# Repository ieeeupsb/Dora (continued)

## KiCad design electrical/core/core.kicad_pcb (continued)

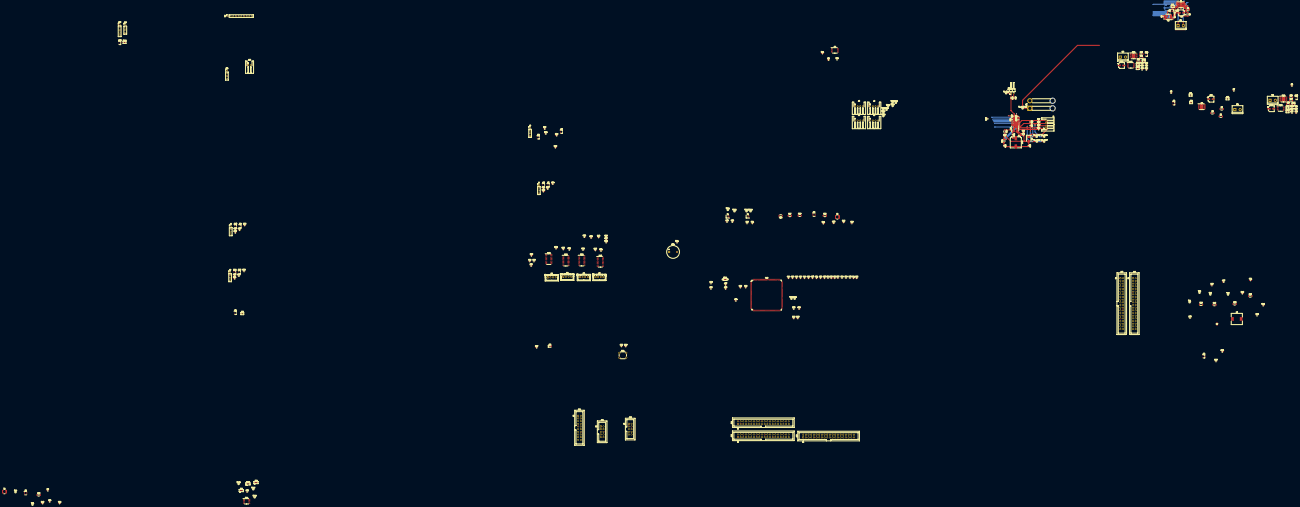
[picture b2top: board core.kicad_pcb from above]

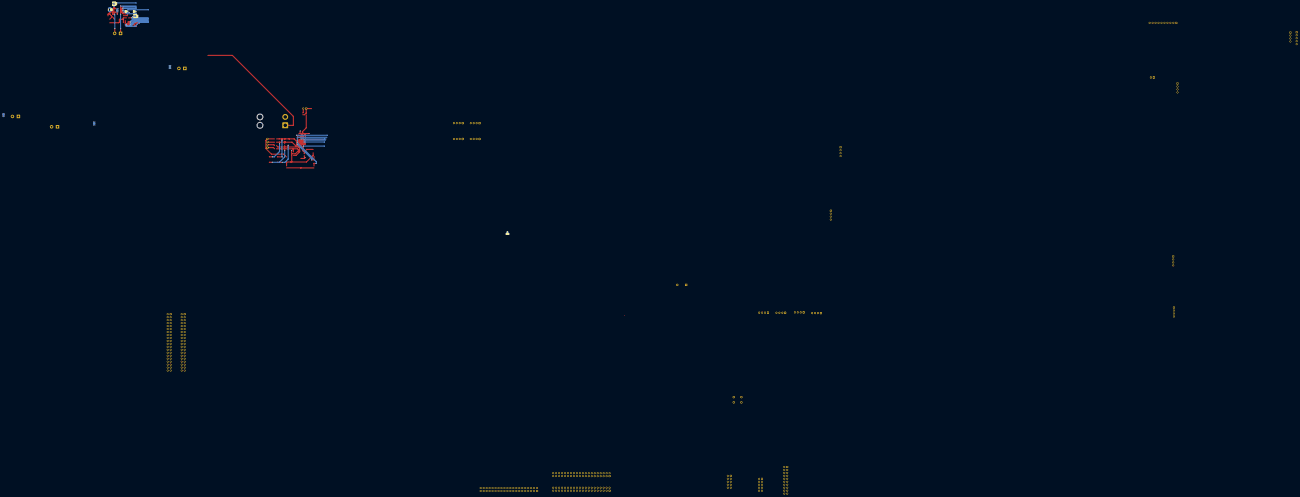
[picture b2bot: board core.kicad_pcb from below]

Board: 4 copper layers, 281 parts (6 on the bottom side), 318 nets.

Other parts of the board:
TP_BATT+1: TestPoint; TestPoint_Pad_D1.0mm

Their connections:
+BATT: TP_BATT+1.1; also elsewhere on the board

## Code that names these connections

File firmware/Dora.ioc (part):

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Mcu.Name=STM32F469IITx
Mcu.Package=LQFP176
Mcu.UserName=STM32F469IITx
PA0/WKUP.Signal=ADCx_IN0
PA1.Signal=S_TIM2_CH2
PA10.Mode=Asynchronous
PA10.Signal=USART1_RX
PA13.Mode=JTAG_5_pins
PA13.Signal=SYS_JTMS-SWDIO
PA14.Mode=JTAG_5_pins
PA14.Signal=SYS_JTCK-SWCLK
PA15.Mode=JTAG_5_pins
PA15.Signal=SYS_JTDI
PA2.Signal=ADCx_IN2
PA3.Signal=ADCx_IN3
PA4.Mode=Slave_8_bits_External_Synchro
PA4.Signal=DCMI_HSYNC
PA5.Signal=S_TIM2_CH1_ETR
PA6.Mode=Slave_8_bits_External_Synchro
PA6.Signal=DCMI_PIXCLK
PA7.Signal=ADCx_IN7
PA9.Mode=Asynchronous
PA9.Signal=USART1_TX
PB0.Signal=ADCx_IN8
PB1.Signal=ADCx_IN9
PB10.Signal=S_TIM2_CH3
PB11.Signal=S_TIM2_CH4
PB13.Mode=Full_Duplex_Master
PB13.Signal=SPI2_SCK
PB14.Mode=Full_Duplex_Master
PB14.Signal=SPI2_MISO
PB15.Mode=Full_Duplex_Master
PB15.Signal=SPI2_MOSI
PB2/BOOT1.GPIOParameters=GPIO_Label
PB2/BOOT1.GPIO_Label=Motor2_IMODE
PB2/BOOT1.Signal=GPIO_Output
PB3.Mode=JTAG_5_pins
PB3.Signal=SYS_JTDO-SWO
PB4.Mode=JTAG_5_pins
PB4.Signal=SYS_JTRST
PB6.Mode=I2C
PB6.Signal=I2C1_SCL
PB7.Mode=I2C
PB7.Signal=I2C1_SDA
PB8.Mode=Slave_8_bits_External_Synchro
PB8.Signal=DCMI_D6
PB9.Mode=Slave_8_bits_External_Synchro
PB9.Signal=DCMI_D7
PC0.Signal=ADCx_IN10
PC1.Signal=ADCx_IN11
PC14/OSC32_IN.Mode=LSE-External-Oscillator
PC14/OSC32_IN.Signal=RCC_OSC32_IN
PC15/OSC32_OUT.Mode=LSE-External-Oscillator
PC15/OSC32_OUT.Signal=RCC_OSC32_OUT
PC2.Signal=ADCx_IN12
PC3.Signal=ADCx_IN13
PC4.Signal=ADCx_IN14
PC5.Signal=ADCx_IN15
PC6.Mode=Slave_8_bits_External_Synchro
PC6.Signal=DCMI_D0
PC7.Mode=Slave_8_bits_External_Synchro
PC7.Signal=DCMI_D1
PC8.Mode=Slave_8_bits_External_Synchro
PC8.Signal=DCMI_D2
PC9.Mode=Slave_8_bits_External_Synchro
PC9.Signal=DCMI_D3
PD10.GPIOParameters=GPIO_Label
PD10.GPIO_Label=D2_DigiPot_WLAT
PD10.Signal=GPIO_Output
PD11.GPIOParameters=GPIO_Label
PD11.GPIO_Label=D2_DigiPot_SHDN
PD11.Signal=GPIO_Output
PD3.Mode=Slave_8_bits_External_Synchro
PD3.Signal=DCMI_D5
PD8.GPIOParameters=GPIO_Label
PD8.GPIO_Label=D1_DigiPot_WLAT
PD8.Signal=GPIO_Output
PD9.GPIOParameters=GPIO_Label
PD9.GPIO_Label=D1_DigiPot_SHDN
PD9.Signal=GPIO_Output
PE11.Signal=S_TIM1_CH2
PE13.Signal=S_TIM1_CH3
PE14.Signal=S_TIM1_CH4
PE4.Mode=Slave_8_bits_External_Synchro
PE4.Signal=DCMI_D4
PE5.Signal=S_TIM9_CH1
PE6.Signal=S_TIM9_CH2
PE7.GPIOParameters=GPIO_Label
PE7.GPIO_Label=Motor1_nFAULT
PE7.Signal=GPIO_Input
PE8.GPIOParameters=GPIO_Label
PE8.GPIO_Label=Motor1_IMODE
PE8.Signal=GPIO_Output
PE9.Signal=S_TIM1_CH1
PF0.Mode=I2C
PF0.Signal=I2C2_SDA
PF1.Mode=I2C
PF1.Signal=I2C2_SCL
PF10.GPIOParameters=GPIO_Label
PF10.GPIO_Label=Driver_Current_Limit_CS2
PF10.Signal=GPIO_Output
PF11.GPIOParameters=GPIO_Label
PF11.GPIO_Label=Motor2_nSLEEP
PF11.Signal=GPIO_Output
PF12.GPIOParameters=GPIO_Label
PF12.GPIO_Label=Motor2_PMODE
PF12.Signal=GPIO_Output
PF13.GPIOParameters=GPIO_Label
PF13.GPIO_Label=Motor2_nFAULT
PF13.Signal=GPIO_Input
PF14.GPIOParameters=GPIO_Label
PF14.GPIO_Label=Motor1_nSLEEP
PF14.Signal=GPIO_Output
PF15.GPIOParameters=GPIO_Label
PF15.GPIO_Label=Motor1_PMODE
PF15.Signal=GPIO_Output
PF2.Signal=GPIO_Input
PF3.Signal=GPIO_Input
PF4.Signal=GPIO_Input
PF5.Signal=GPIO_Input
PF6.Signal=S_TIM10_CH1
PF7.Signal=GPIO_Input
PF8.Signal=GPIO_Input
PF9.GPIOParameters=GPIO_Label
PF9.GPIO_Label=Driver_Current_Limit_CS1
PF9.Signal=GPIO_Output
PG0.GPIOParameters=GPIO_Label
PG0.GPIO_Label=Rotary_SW
PG0.Signal=GPIO_Input
PG1.GPIOParameters=GPIO_Label
PG1.GPIO_Label=Rotary_CLK
PG1.Signal=GPIO_Input
PG10.GPIOParameters=GPIO_Label
PG10.GPIO_Label=IR_SEL0
PG10.Signal=GPIO_Output
PG11.GPIOParameters=GPIO_Label
PG11.GPIO_Label=IR_SEL1
PG11.Signal=GPIO_Output
PG12.GPIOParameters=GPIO_Label
PG12.GPIO_Label=IR_SEL2
PG12.Signal=GPIO_Output
PG13.GPIOParameters=GPIO_Label
PG13.GPIO_Label=WP
PG13.Signal=GPIO_Output
PG14.GPIOParameters=GPIO_Label
PG14.GPIO_Label=Battery_Overcurrent
PG14.Signal=GPIO_Input
PG2.GPIOParameters=GPIO_Label
PG2.GPIO_Label=Rotary_DT
PG2.Signal=GPIO_Input
PG3.GPIOParameters=GPIO_Label
PG3.GPIO_Label=LEFT_ENC1
PG3.Signal=GPIO_Input
PG4.GPIOParameters=GPIO_Label
PG4.GPIO_Label=LEFT_ENC2
PG4.Signal=GPIO_Input
PG5.GPIOParameters=GPIO_Label
PG5.GPIO_Label=RIGHT_ENC1
PG5.Signal=GPIO_Input
PG6.GPIOParameters=GPIO_Label
PG6.GPIO_Label=RIGHT_ENC2
PG6.Signal=GPIO_Input
PG9.Mode=Slave_8_bits_External_Synchro
PG9.Signal=DCMI_VSYNC
PH0/OSC_IN.Mode=HSE-External-Oscillator
PH0/OSC_IN.Signal=RCC_OSC_IN
PH1/OSC_OUT.Mode=HSE-External-Oscillator
PH1/OSC_OUT.Signal=RCC_OSC_OUT
PH2.GPIOParameters=GPIO_Label
PH2.GPIO_Label=OLED_EN
PH2.Signal=GPIO_Output
PH3.GPIOParameters=GPIO_Label
PH3.GPIO_Label=Ultra_EN
PH3.Signal=GPIO_Output
PH4.GPIOParameters=GPIO_Label
PH4.GPIO_Label=IR_EN
PH4.Signal=GPIO_Output
PH5.GPIOParameters=GPIO_Label
PH5.GPIO_Label=RPi_EN
PH5.Signal=GPIO_Output
PH6.GPIOParameters=GPIO_Label
PH6.GPIO_Label=Camera_EN
PH6.Signal=GPIO_Output
PH7.GPIOParameters=GPIO_Label
PH7.GPIO_Label=LoRa_EN
PH7.Signal=GPIO_Output
PI0.GPIOParameters=GPIO_Label
PI0.GPIO_Label=Ultra1_TRIG
PI0.Signal=GPIO_Output
PI1.GPIOParameters=GPIO_Label
PI1.GPIO_Label=Ultra1_ECHO
PI1.Signal=GPIO_Input
PI3.GPIOParameters=GPIO_Label
PI3.GPIO_Label=Ultra2_TRIG
PI3.Signal=GPIO_Output
PI4.GPIOParameters=GPIO_Label
PI4.GPIO_Label=Ultra2_ECHO
PI4.Signal=GPIO_Input
PI5.GPIOParameters=GPIO_Label
PI5.GPIO_Label=Ultra3_TRIG
PI5.Signal=GPIO_Output
PI6.GPIOParameters=GPIO_Label
PI6.GPIO_Label=Ultra3_ECHO
PI6.Signal=GPIO_Input
PI7.GPIOParameters=GPIO_Label
PI7.GPIO_Label=Ultra4_TRIG
PI7.Signal=GPIO_Output
PI8.GPIOParameters=GPIO_Label
PI8.GPIO_Label=Ultra4_ECHO
PI8.Signal=GPIO_Input
RCC.SYSCLKFreq_VALUE=180000000
RCC.SYSCLKSource=RCC_SYSCLKSOURCE_PLLCLK
board=custom

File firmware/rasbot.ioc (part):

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Mcu.Name=STM32F103C(8-B)Tx
Mcu.Package=LQFP48
Mcu.UserName=STM32F103C8Tx
PA13.Mode=Serial_Wire
PA13.Signal=SYS_JTMS-SWDIO
PA14.Mode=Serial_Wire
PA14.Signal=SYS_JTCK-SWCLK
PC14-OSC32_IN.Mode=LSE-External-Oscillator
PC14-OSC32_IN.Signal=RCC_OSC32_IN
PC15-OSC32_OUT.Mode=LSE-External-Oscillator
PC15-OSC32_OUT.Signal=RCC_OSC32_OUT
PD0-OSC_IN.Mode=HSE-External-Oscillator
PD0-OSC_IN.Signal=RCC_OSC_IN
PD1-OSC_OUT.Mode=HSE-External-Oscillator
PD1-OSC_OUT.Signal=RCC_OSC_OUT
RCC.SYSCLKFreq_VALUE=72000000
RCC.SYSCLKSource=RCC_SYSCLKSOURCE_PLLCLK
board=custom

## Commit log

2019-06-19 Backlink to CADLAB.io has been added.
2019-06-19 [PCB] Project Initialization
2019-06-20 [Firmware] Skeleton Code
2019-06-20 [PCB] MCU Decoupling Capacitors
2019-06-20 [PCB] MCU Crystal
2019-06-20 [Firmware] Ignore Eclipse Files
2019-06-20 [PCB] Assign Footprints
2019-06-20 [PCB & Firmware] SWD Interface
2019-06-20 [PCB] Reset Button, Power LED, BOOT pins and LSE Crystal
2019-06-20 [PCB] Crystal Capacitor Sizing
2019-06-20 [PCB & Firmware] SWD Connector and Reset Button Footprint and Firmware LSE Enable
2019-06-20 [PCB] Connect LSE to MCU
2019-06-20 [PCB & Firmware] Motors PWM Signal MCU Pins
2019-06-20 [PCB & Firmware] Line Sensors MCU Pins
2019-06-20 [PCB & Firmware] I2C for LCD SSD1306 MCU Pins
2019-06-20 [PCB & Firmware] Light Sensor MCU Pin
2019-06-26 IR matrix
2019-07-07 Infrared index starts at 0
2019-07-09 Use Buses for IR sensors
2019-07-22 IR matrix complete minus control transistor
2019-07-22 AO3400 Symbol added to library
2019-07-22 MOSFET model added
2019-07-22 IR Matrix - Missing Supply Connection
2019-07-22 Initial Symbol for DRV8873S
2019-07-24 Resistor value corrected
2019-07-25 Added 0 ohm resistor to power switch
2019-07-25 Fixed AO3400 symbol
2019-07-25 Fixed DRV8873 symbol
2019-07-25 Buzzer and RGB LED interfaces
2019-07-25 Increased Resistance
2019-07-26 Description of the project
2019-07-26 Notes about branch protections
2019-07-27 STM32F407 and JLink
2019-07-28 Connect IR Matrix to MCU
2019-07-28 Optimized IR MCU pins
2019-07-28 Size Crystals
2019-07-28 Fix IR Sensors
2019-07-28 Grammar revision
2019-07-28 Fix resistor IR Matrix
2019-07-28 Added BQ76925 KiCAD symbol
2019-07-28 Fix Merges
2019-07-28 Clean Project
2019-07-28 Fix and Anotate design
2019-07-28 MCU connections, OLED and Sonar
2019-07-28 Connect Ultrasonic Sensors
2019-07-29 Rotary Encoder
2019-07-29 Fix pins
2019-07-29 Battery monitor .sch early commit. Not yet included in hierarchical sheet
2019-07-29 Moved Power inside the project
2019-07-30 Documentation and new sense resistor added to rasbot.lib
2019-07-30 Cell voltage, BATT+, current sensor and VCTL changed. Changes to lib changed the other .sch
2019-07-30 Current sensor resistor datasheet
2019-07-30 Thermistor added
2019-07-30 Thermistor doc
2019-08-05 Project divided into Core and Plugins
2019-08-14 Add 256kB EEPROM to the project
2019-08-14 Add pull-up resistor to the SDA line
2019-08-14 pull-up resistor on SCL and WP
    According to Application note AN1028 WP can't be left floating and both I2C pins and WP should have a pull-up
2019-08-14 Decoupling cap as AN1028 suggests
2019-08-14 Tidy up
    Moved around circuit blocks
2019-08-14 Changed WP pull up to 10K Ohms to reduce power draw
2019-08-14 A0 and A1 are not connected according to datasheet
2019-08-14 EEPROM is SOIC
2019-08-14 Fix libraries
2019-08-14 Fixes all around
2019-08-14 Ignore local backup and rescue files
2019-08-14 Motor Driver schematic
2019-08-14 fix libraries and annotate schematic
2019-08-15 Added DRV8876
2019-08-15 Update Libraries
2019-08-15 Library update
2019-08-16 Preliminary circuitry for the DRV8876 motor driver
2019-08-16 Fix DRV8876 Library
2019-08-16 Add connection from PAD to GND
2019-08-16 Add missing transistor to sensor sheet
2019-08-17 Add current limiting resistor and bulk capacitor
2019-08-17 Update hierarchical labels
2019-08-21 Prettify Motor Driver Schematic
2019-08-21 Complete circuit of the available Logitech USB mouse
2019-08-21 Add RPi connectors and fix tons of bugs
2019-08-21 Partial circuit of the HP PS/2 mouse
2019-08-21 Subdivided sheet power
2019-08-21 Size SEPIC inductor and MOSFETs
2019-08-21 Fix division in power
2019-08-21 Inductor Footprint
2019-08-21 Supply and Enable
2019-08-21 MOSFET Footprint
2019-08-21 SEPIC rectify output
2019-08-21 redid NTC connection to the BMS and changed current sense resistors
2019-08-21 NTC resistance changed
2019-08-21 Fix connection to Vin
2019-08-21 Fix Library
2019-08-21 Fix Driver
2019-08-24 Give Up SEPIC and 9V LDO design
2019-08-24 Designed 5V and 3.3V (MCU) LDOs
2019-08-24 Raspberry Pi Buck
2019-08-24 Added Test Points
2019-08-24 Deprecated Files Removed
2019-08-24 added LoRa Module
2019-08-25 Fix merge problems
2019-08-26 Updated Driver to DRV8874-Q1
2019-08-26 Placed DCMI, Clock Sources and Debug pins
2019-08-26 STM32F469IIT6 in schematic and firmware init
2019-08-28 Tune crystals loading capacitance
2019-08-30 Assign Footprints
2019-08-30 Fix RPI
2019-08-30 added camera and core MCU pins
2019-08-31 Added camera, Motor driver PWM, RGB LEDs
2019-08-31 Connected LoRa and OLED
2019-08-31 Fix LED footprint
2019-09-08 Motor sense added
2019-09-08 BMS i2c
2019-09-08 IR merged with core
2019-09-08 Camera I2C
2019-09-09 Lots of Connections
2019-09-09 Expose Pins
2019-09-09 Annotate Schematic
2019-09-09 Missing Footprints
2019-09-09 Digipot symbol
2019-09-16 Fix camera shutdown bug
2019-10-10 Driver IOs
2019-10-10 Filter capacitor added
2019-10-10 Anotation
2019-10-10 Placeholder TVS diode
2019-10-10 Pull up for overcurrent output and more protection diode
2019-10-10 Fix Driver Connections
2019-10-10 5V buck
2019-10-10 Fancy sheet
2019-10-11 Buck 3V3
2019-10-11 Clean Power Sheet
2019-10-11 Annotation
2019-10-12 tidy up power sheet
2019-10-19 3.3 - 5V level shifter sonar with 2n3904
2019-10-21 add probe points in sonar
2019-10-25 cleanup ultrassonic
2019-10-25 Added DigiPot to the Drivers for current limit control
2019-10-25 tidy up driver
2019-10-25 straightned label
2019-10-25 Connect WLAT and SHDN
2019-10-25 BMX055 symbol creation
2020-03-06 Updated ultrassonic level shifter
2020-03-06 Several updates. Can't remember them all
2020-04-25 lots of changes
2020-04-25 Remove unused +9V LDO
2020-04-25 Reannotated after LDO romval
2020-04-25 Changed RPi connector
2020-04-26 Removed ghost pin and change SDA to Bidirectional
2020-04-28 Added secondary MCU to IR board
2020-04-28 Connected IR_SEL lines to secondary MCU
2020-04-28 Re-annotated Schematic
2020-04-28 Refined IR board connections
2020-05-01 Remove power toggle button
2020-05-01 Move IR board to different project
2020-05-03 Revised BMS circuitry
2020-05-03 Fix all ERC errors
2020-05-03 [IR] minor tweak
2020-05-03 Fix errors and JTAG connectors
2020-05-03 Fix bug in BMS connections
2020-05-04 Make encoder connectors of JST type
2020-05-05 Replace MCU with more pin variant
2020-05-10 Add buck symbols
2020-05-10 Changed RPi Buck to new model in order to support Jetson Nano boards
    Fixed a bug in the Ultrassonic sensors level-shifters
2020-05-10 revert changes to Level-shifters. Optimize for single-direction operation
2020-05-11 Review capacitors and warnings
2020-05-11 Remove LoRa from Project
2020-05-11 Reannotated Schematics
2020-05-13 Reviewed uC decoupling
2020-05-13 Rearranged uC sheet
2020-05-15 Minor BMS revision and added bulk capacitor footprints
2020-05-15 Reannotated schematic
2020-07-20 connections
2020-07-20 Expansion header
2021-03-02 Add connector for IR board and footprints
2021-03-07 Added buck to IR_board - Same as Main board buck. Added footprint for 12AWG wire connector (XT60) - need to check size of the wire
2021-03-10 .gitignore fix
2021-03-29 Make Dora have 4 motors
2021-04-10 Modified XT60 footprint
2021-05-13 MCP41HV51 symbol - SDO changed from output to tri-state
2021-05-13 Added TVS diode and missing footprints
2021-07-06 Schematic changes and some docs added
2021-07-06 Starting main board layout
2021-07-06 Updated doc and reorganization of components in main board layout
2021-07-12 Changes to schematic. QOL changes to I2C TPs
2021-07-12 Updated to do list in docs
2021-07-13 BMS TPs QoL change
2021-07-13 BMS layout try
2021-07-13 Motor 1 try layout
2021-07-15 Larger pad and holes in the XT60 footprint
